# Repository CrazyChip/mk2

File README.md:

# mk2
===
MkII clone with LUFA firmware.

### Features:
* ISP-10, ISP-6, PDI, TPI connectors
* Atmega16U2 based
* 3.3V - 5V selector
* uses Atmega's internal 3.3V regulator (no external regulator)
* no output buffer, minimal number of parts

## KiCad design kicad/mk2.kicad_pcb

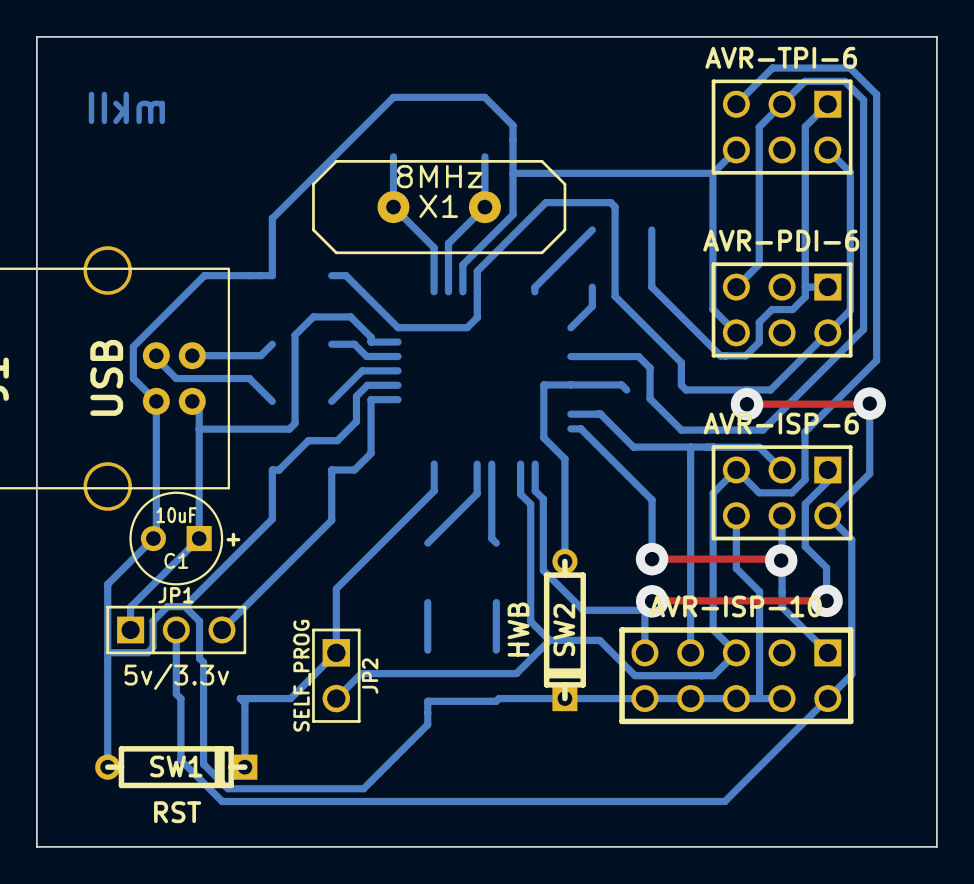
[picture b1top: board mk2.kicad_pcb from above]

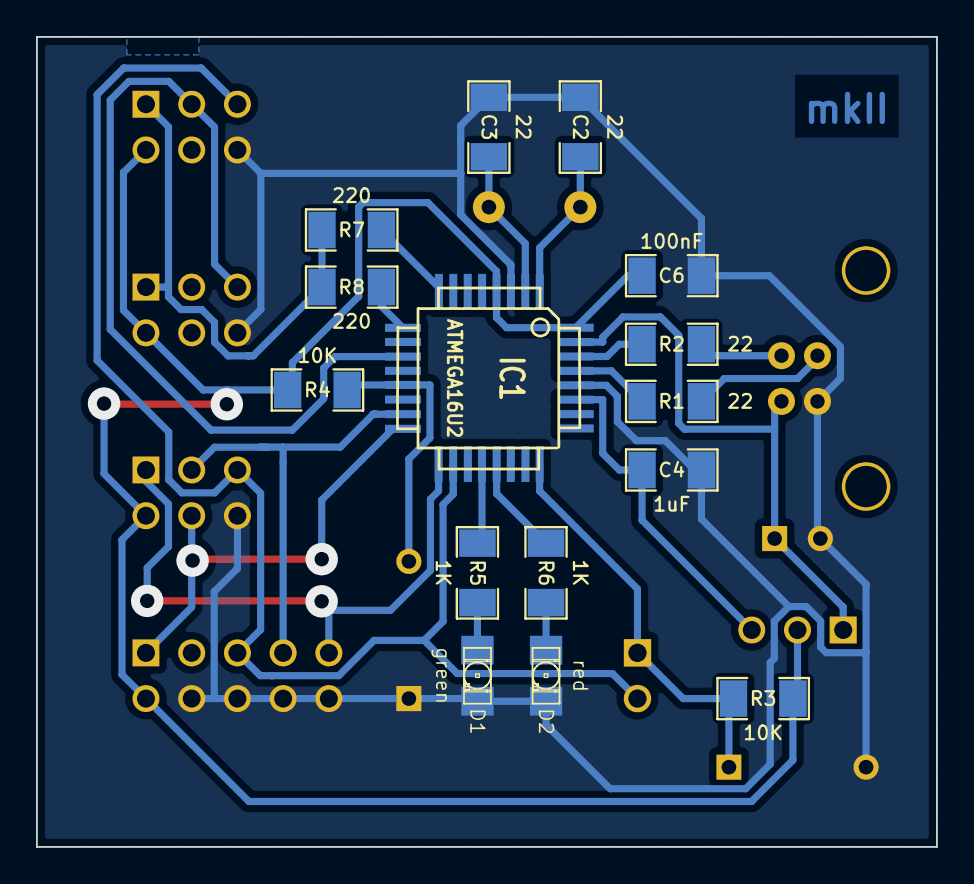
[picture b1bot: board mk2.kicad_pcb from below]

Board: 2 copper layers, 50.0 x 45.0 mm, 26 parts (15 on the bottom side), 24 nets.

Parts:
C1: 10uF; C1V5
C2, C3: 22; SM1206
C4: 1uF; SM1206
C6: 100nF; SM1206
CON1: AVR-ISP-6; pin_array_3x2
CON2: AVR-PDI-6; pin_array_3x2
CON3: AVR-TPI-6; pin_array_3x2
CON4: AVR-ISP-10; PIN_ARRAY_5x2
D1: green; LED-1206
D2: red; LED-1206
IC1: ATMEGA16U2; TQFP32
J1: USB; USB_B
JP1: 5v/3.3v; PIN_ARRAY_3X1
JP2: SELF_PROG; PIN_ARRAY_2X1
R1, R2: 22; SM1206
R3, R4: 10K; SM1206
R5, R6: 1K; SM1206
R7, R8: 220; SM1206
SW1: RST; D3
SW2: HWB; D3
X1: 8MHz; HC-18UV

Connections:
GND: C1.2, C2.1, C3.1, C4.1, C6.2, CON1.6, CON2.6, CON3.6, CON4.4, CON4.6, CON4.8, CON4.10, D1.2, D2.2, IC1.3, IC1.28, J1.4, SW1.1, SW2.2
IO_C: CON2.5, CON3.3, IC1.11
IO_D: CON2.1, CON3.1, R7.2, R8.2
MISO: CON1.1, CON4.9, IC1.17
MOSI: CON1.4, CON4.1, IC1.16
unnamed: IC1.21, R6.1
unnamed: IC1.20, R5.1
unnamed: IC1.9, R8.1
unnamed: IC1.8, R7.1
unnamed: D2.1, R6.2
unnamed: D1.1, R5.2
unnamed: J1.2, R2.2
unnamed: J1.3, R1.1
unnamed: IC1.30, R2.1
unnamed: IC1.29, R1.2
unnamed: IC1.24, JP2.1, R3.1, SW1.2
unnamed: IC1.13, R4.1, SW2.1
unnamed: C2.2, IC1.1, X1.2
unnamed: C3.2, IC1.2, X1.1
RST: CON1.5, CON3.5, CON4.5, IC1.18, JP2.2
SCK: CON1.3, CON4.7, IC1.15
UCAP: C4.2, IC1.27, JP1.3
VBUS: C1.1, IC1.31, J1.1, JP1.1
VCC: C6.1, CON1.2, CON2.2, CON3.2, CON4.2, IC1.4, IC1.32, JP1.2, R3.2, R4.2

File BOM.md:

| No | Designator | Package | Quantity | Designation | Price | Supplier's ref |
| ---- | ---- | ---- | ---- | ---- | ---- | ---- |
| 1 | J1 | USB_B | 1 | USB | 1.5 | CLI812 |
| 2 | IC1 | TQFP32 | 1 | ATMEGA16U2 | 15.06 | 7153791 |
| 3 | R7,R8 | SM1206 | 2 | 220 | 0.1 | RM222 |
| 4 | R4,R3 | SM1206 | 2 | 10K | 0.1 | RM410 |
| 5 | R5,R6 | SM1206 | 2 | 1K | 0.1 | RM310 |
| 6 | C6 | SM1206 | 1 | 100nF | 0.15 | KM510X6 |
| 7 | C3,C2 | SM1206 | 2 | 22 | 0.1 | KM122N6 |
| 8 | R2,R1 | SM1206 | 2 | 22 | 0.1 | RM122 |
| 9 | C4 | SM1206 | 1 | 1uF | 0.2 | KM610Y6 |
| 10 | CON4 | PIN_ARRAY_5x2 | 1 | AVR-ISP-10 | 1.8 | CJK4402 |
|  | CON3 | PIN_ARRAY_3x2 | 1 | AVR-TPI-6 |  |  |
|  | CON2 | PIN_ARRAY_3x2 | 1 | AVR-PDI-6 |  |  |
|  | CON1 | PIN_ARRAY_3x2 | 1 | AVR-ISP-6 |  |  |
|  | JP1 | PIN_ARRAY_3X1 | 1 | 5v/3.3v |  |  |
|  | JP2 | PIN_ARRAY_2X1 | 1 | SELF_PROG |  |  |
| 11 | D2 | LED-1206 | 1 | red | 0.2 | PLDKS06G |
| 12 | D1 | LED-1206 | 1 | green | 0.25 | PLDKS06ZS |
| 13 | X1 | HC-18UV | 1 | 8MHz | 1.9 | QK08M |
| 14 | SW1,SW2 | D3 | 2 | HWB,RST buttons | 0.5 | CPR024 |
| 15 | C1 | C1V5 | 1 | 10uF | 0.1 | KE10/6 |
| 16 | JP | JUMPER | 2 | SELECTOR | 0.1 | CJT5R |

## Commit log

2014-12-23 Update BOM.md
    fix table
2014-12-23 Update BOM.md
    fix 2
2014-12-23 BOM updated
    added SMD resistor
2014-12-24 schematic
    initial schematic, Atmega and USB connections
2014-12-24 BOM
    bom fix3
2014-12-25 initial schematic
    Schematic with FET output buffer
2014-12-26 updated schematic
    Removed output buffers and external 3.3V regulator
    Crystal changed to 8MHz
    Pullups changed to 10K
    Added jumper for self-programming
2014-12-26 BOM updated
    removed some parts
2014-12-26 PCB
    One-sided PCB prepared
2014-12-26 Update README.md
    added list of features
2014-12-27 final BOM
    Full list of materials
2014-12-27 BOM updated
    jumpers added
2014-12-27 PCB update
    Updated silkscreen
